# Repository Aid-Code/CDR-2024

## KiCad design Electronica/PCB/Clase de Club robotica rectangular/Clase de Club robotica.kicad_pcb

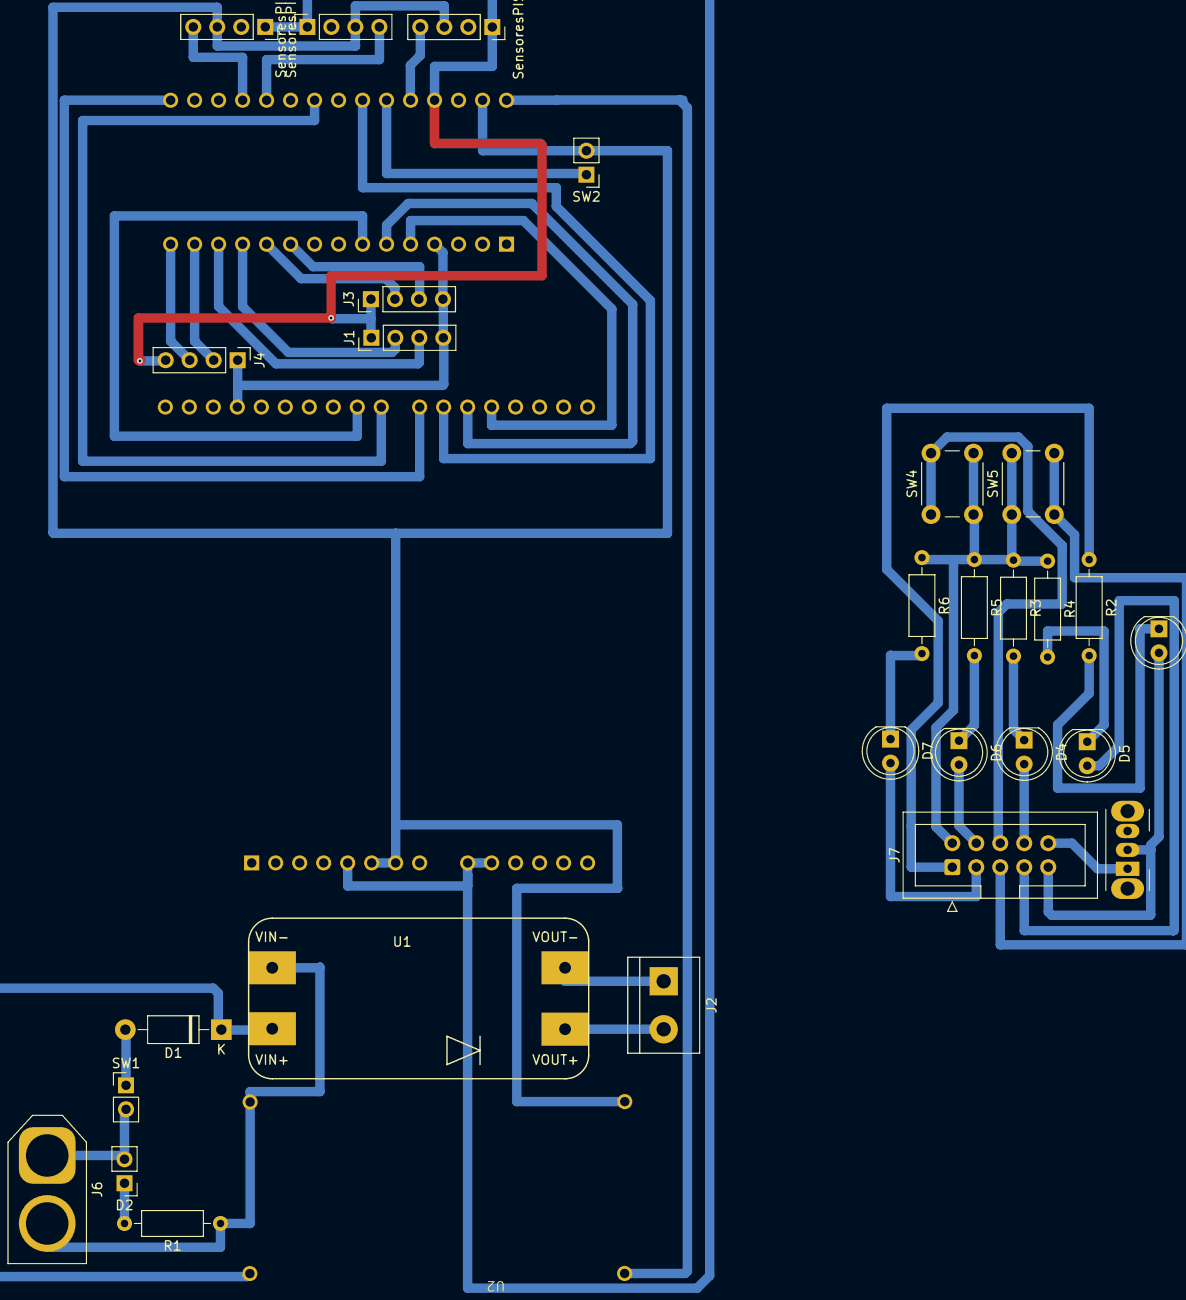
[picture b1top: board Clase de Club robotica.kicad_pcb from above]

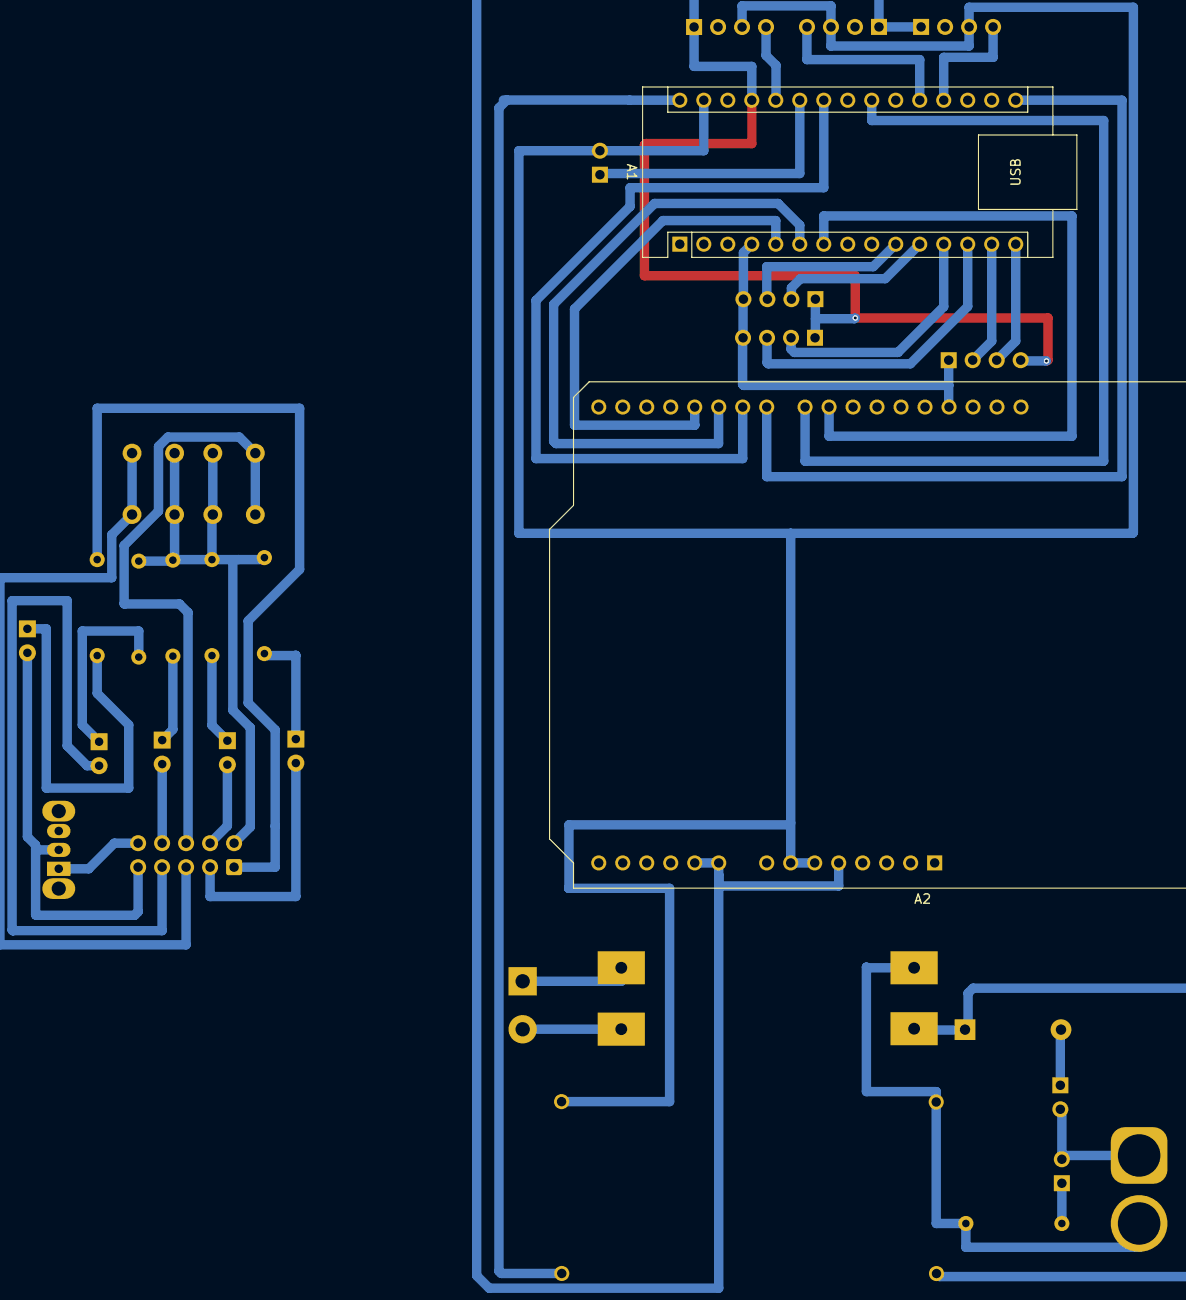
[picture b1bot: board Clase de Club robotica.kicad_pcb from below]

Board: 2 copper layers, 31 parts (2 on the bottom side), 39 nets.

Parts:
A1: Arduino_Nano_v3.x; Arduino_Nano
A2: MONSTER SHIELD; Arduino_UNO_R3
D1: 1N4007; D_DO-41_SOD81_P10.16mm_Horizontal
D2: LED; PinHeader_1x02_P2.54mm_Vertical
D3, D4, D5, D6, D7: LED; LED_D5.0mm
J1: Ultrasonico 1; PinHeader_1x04_P2.54mm_Vertical
J2: Screw_Terminal_01x02; TerminalBlock_bornier-2_P5.08mm
J3: Ultrasonico 2; PinHeader_1x04_P2.54mm_Vertical
J4: Ultrasonico 3; PinHeader_1x04_P2.54mm_Vertical
J6: Screw_Terminal_01x02; AMASS_XT60-M_1x02_P7.20mm_Vertical
J7: Conn_02x05_Counter_Clockwise; IDC-Header_2x05_P2.54mm_Vertical
R1: R_US; R_Axial_DIN0207_L6.3mm_D2.5mm_P10.16mm_Horizontal
R2: 660; R_Axial_DIN0207_L6.3mm_D2.5mm_P10.16mm_Horizontal
R3, R4, R5, R6: 220; R_Axial_DIN0207_L6.3mm_D2.5mm_P10.16mm_Horizontal
SW1: SW_SPST; PinHeader_1x02_P2.54mm_Vertical
SW2: SW_Push; PinHeader_1x02_P2.54mm_Vertical
SW3: SW_SPST; SW_Slide_SPDT_Angled_CK_OS102011MA1Q
SW4, SW5: SW_Push; SW_PUSH_6mm
SensoresPISO1, SensoresPISO2, SensoresPISO3: Conn_01x04; PinSocket_1x04_P2.54mm_Vertical
U1: MT3608_module
U2: Step Down

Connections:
+5V: A1.27 (+5V), A2.5 (+5V), A2.9 (A0), A2.10 (A1), J1.1, J3.1, J4.4, SensoresPISO1.1, SensoresPISO2.1, SensoresPISO3.1
AIN1 MONSTER SHIELD: A1.16 (D13), A2.22 (D7)
AIN2 MONSTER SHIELD: A1.22 (A3), A2.23 (D8)
BIN 1 MONSTER SHIELD: A1.5 (D2), A2.19 (D4)
BIN 2 MONSTER SHIELD: A1.7 (D4), A2.24 (D9)
BOTON: A1.25 (A6), SW2.1
ECHO 1: A1.13 (D10), J1.3
ECHO 2: A1.10 (D7), J3.3
ECHO 3: A1.14 (D11), J4.2
Earth: J6.2, J7.1, R1.1, R2.1, U1.VIN-, U2.VIN-
GND: A1.4 (GND), A1.29 (GND), A2.6 (GND), A2.7 (GND), A2.29 (GND), J1.4, J3.4, J4.1, J7.2, R3.1, R4.1, R5.1, R6.1, SW2.2, SW4.2, SW5.1, SensoresPISO1.3, SensoresPISO2.3, SensoresPISO3.3, U2.VOUT-
unnamed: D1.2 (A), SW1.1 (A)
unnamed: D2.2 (A), J6.1, SW1.2 (B)
unnamed: D2.1 (K), R1.2
unnamed: D3.2 (A), J7.9, SW3.2 (B)
unnamed: D3.1 (K), R2.2
unnamed: D4.2 (A), J7.8
unnamed: D4.1 (K), R3.2
unnamed: D5.2 (A), J7.7
unnamed: D5.1 (K), R4.2
unnamed: D6.2 (A), J7.4
unnamed: D6.1 (K), R5.2
unnamed: D7.2 (A), J7.3
unnamed: D7.1 (K), R6.2
unnamed: J2.1, U1.VOUT-
unnamed: J2.2, U1.VOUT+
unnamed: J7.5, SW5.2
unnamed: J7.6, SW4.1
unnamed: J7.10, SW3.1 (A)
PWM A MONSTER SHIELD: A1.6 (D3), A2.20 (D5)
PWM B MONSTER SHIELD: A1.24 (A5), A2.21 (D6)
SENSOR DE PISO 1: A1.26 (A7), SensoresPISO1.4
SENSOR DE PISO 2: A1.20 (A1), SensoresPISO2.4
SENSOR DE PISO 3: A1.19 (A0), SensoresPISO3.4
STEP DOWN: D1.1 (K), U1.VIN+, U2.VIN+
TRIG 1: A1.12 (D9), J1.2
TRIG 2: A1.11 (D8), J3.2
TRIG 3: A1.15 (D12), J4.3
VIN: A1.30 (VIN), U2.VOUT+

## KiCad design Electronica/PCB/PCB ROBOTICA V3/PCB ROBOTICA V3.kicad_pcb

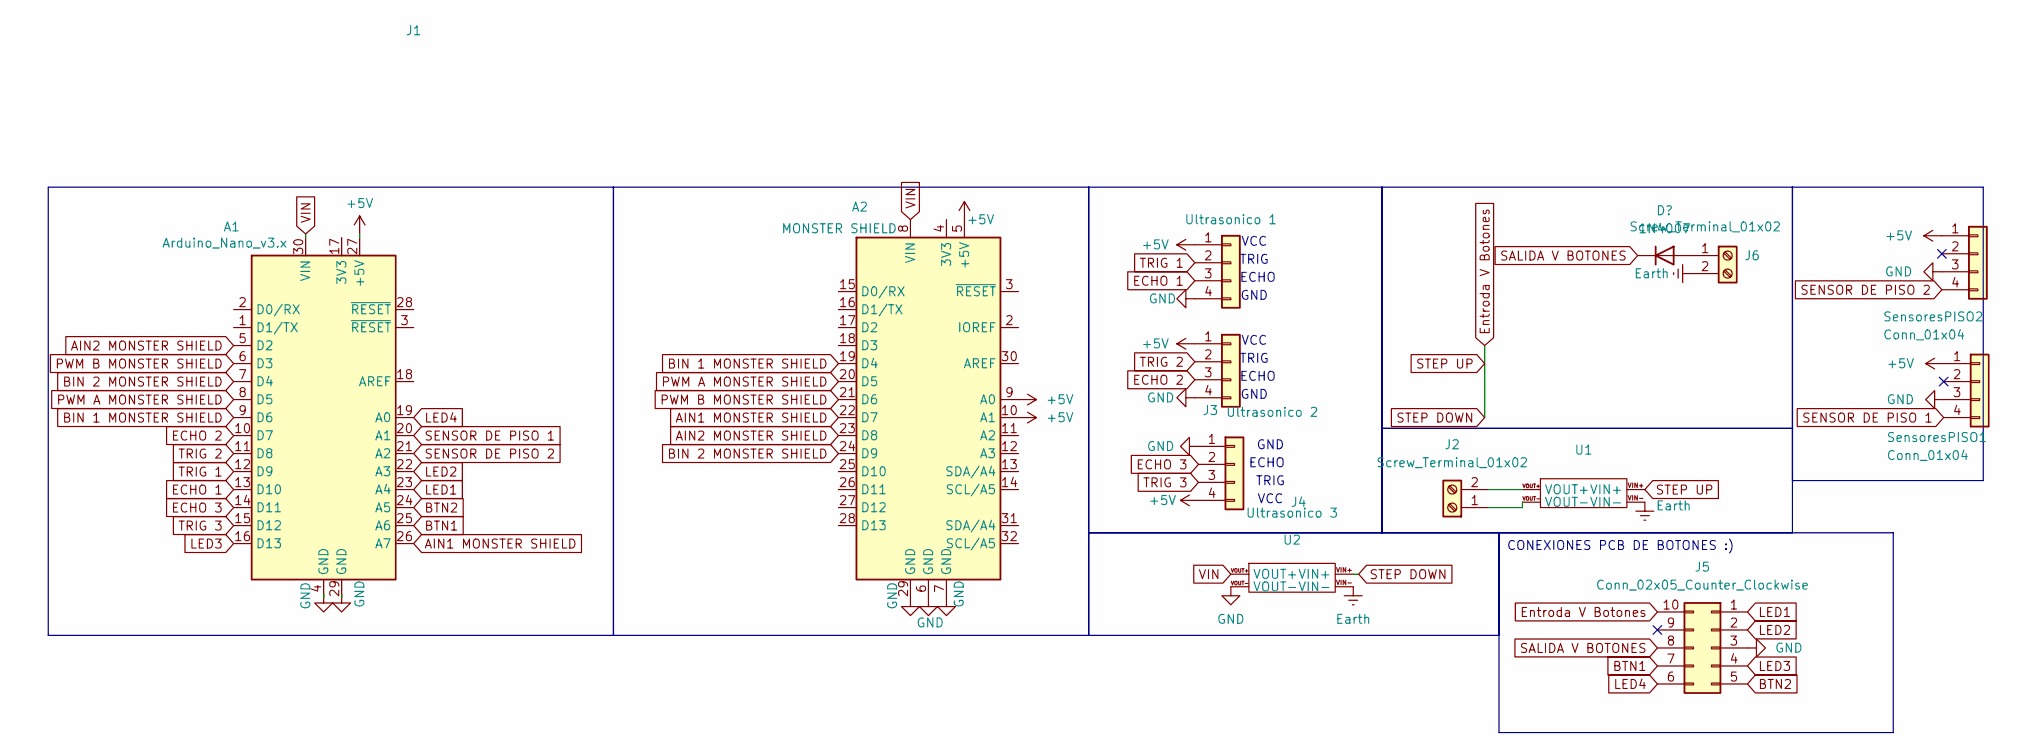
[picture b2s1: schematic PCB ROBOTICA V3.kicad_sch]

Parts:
A1: Arduino_Nano_v3.x; Arduino_Nano
A2: MONSTER SHIELD; Arduino_UNO_R3
J1: Ultrasonico 1; PinHeader_1x04_P2.54mm_Vertical
J2: Screw_Terminal_01x02; TerminalBlock_bornier-2_P5.08mm
J3: Ultrasonico 2; PinHeader_1x04_P2.54mm_Vertical
J4: Ultrasonico 3; PinHeader_1x04_P2.54mm_Vertical
J5: Conn_02x05_Counter_Clockwise; IDC-Header_2x05_P2.54mm_Vertical
J6: Screw_Terminal_01x02; AMASS_XT60-M_1x02_P7.20mm_Vertical
SensoresPISO1, SensoresPISO2: Conn_01x04; PinSocket_1x04_P2.54mm_Vertical
U1: MT3608_module
U2: Step Down

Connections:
+5V: A1.27 (+5V), A2.5 (+5V), A2.9 (A0), A2.10 (A1), J1.1, J3.1, J4.4, SensoresPISO1.1, SensoresPISO2.1
AIN1 MONSTER SHIELD: A1.26 (A7), A2.22 (D7)
AIN2 MONSTER SHIELD: A1.5 (D2), A2.23 (D8)
BIN 1 MONSTER SHIELD: A1.9 (D6), A2.19 (D4)
BIN 2 MONSTER SHIELD: A1.7 (D4), A2.24 (D9)
BTN1: A1.25 (A6), J5.7
BTN2: A1.24 (A5), J5.5
ECHO 1: A1.13 (D10), J1.3
ECHO 2: A1.10 (D7), J3.3
ECHO 3: A1.14 (D11), J4.2
Earth: J6.2, U1.VIN-, U2.VIN-
Entroda V Botones: J5.10, U1.VIN+, U2.VIN+
GND: A1.4 (GND), A1.29 (GND), A2.6 (GND), A2.7 (GND), A2.29 (GND), J1.4, J3.4, J4.1, J5.3, SensoresPISO1.3, SensoresPISO2.3, U2.VOUT-
LED1: A1.23 (A4), J5.1
LED2: A1.22 (A3), J5.2
LED3: A1.16 (D13), J5.4
LED4: A1.19 (A0), J5.6
unnamed 17: J6.1; also elsewhere on the board
unnamed: J2.1, U1.VOUT-
unnamed: J2.2, U1.VOUT+
PWM A MONSTER SHIELD: A1.8 (D5), A2.20 (D5)
PWM B MONSTER SHIELD: A1.6 (D3), A2.21 (D6)
SALIDA V BOTONES: J5.8; also elsewhere on the board
SENSOR DE PISO 1: A1.20 (A1), SensoresPISO1.4
SENSOR DE PISO 2: A1.21 (A2), SensoresPISO2.4
TRIG 1: A1.12 (D9), J1.2
TRIG 2: A1.11 (D8), J3.2
TRIG 3: A1.15 (D12), J4.3
VIN: A1.30 (VIN), A2.8 (VIN), U2.VOUT+

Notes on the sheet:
CONEXIONES PCB DE BOTONES :)
ECHO
TRIG
GND
VCC

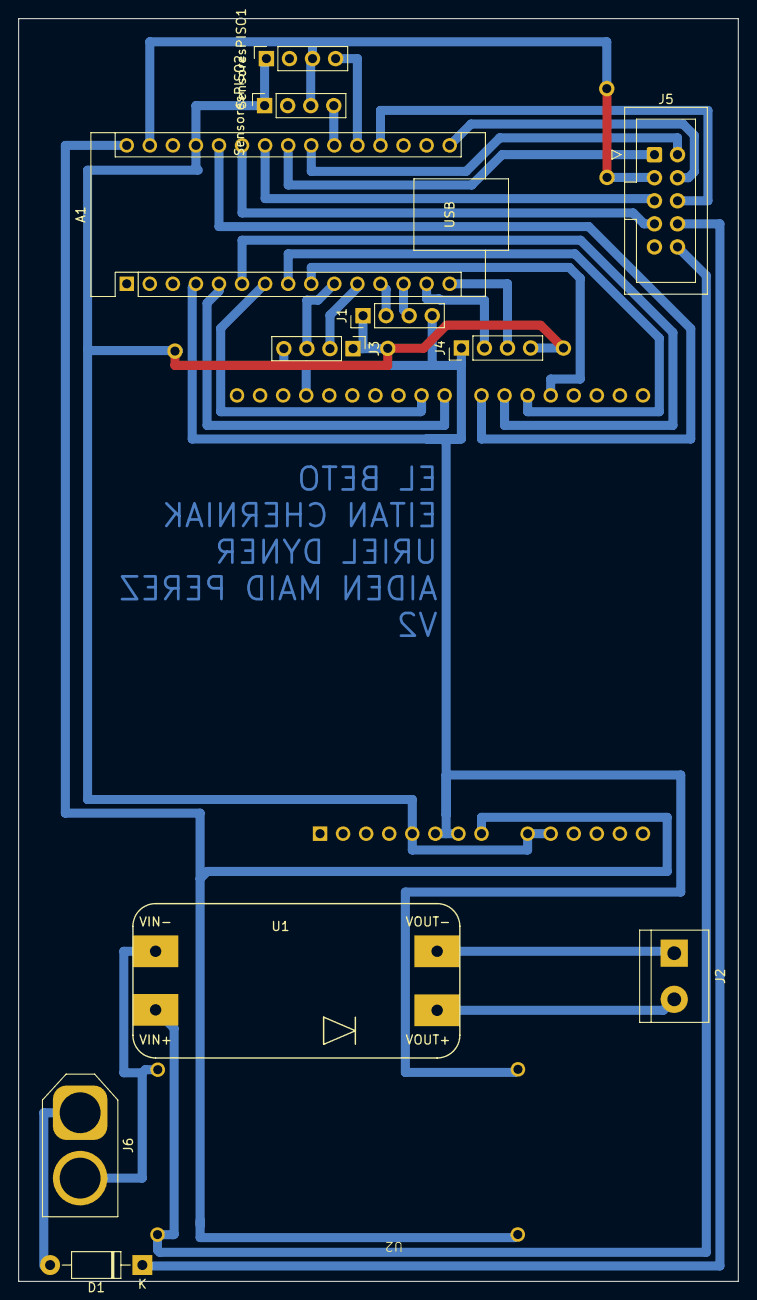
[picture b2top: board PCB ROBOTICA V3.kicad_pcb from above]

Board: 2 copper layers, 79.2 x 139.1 mm, 13 parts (1 on the bottom side), 29 nets.

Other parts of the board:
D1: 1N4007; D_DO-41_SOD81_P10.16mm_Horizontal

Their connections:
unnamed 17: D1.2 (A); also elsewhere on the board
SALIDA V BOTONES: D1.1 (K); also elsewhere on the board

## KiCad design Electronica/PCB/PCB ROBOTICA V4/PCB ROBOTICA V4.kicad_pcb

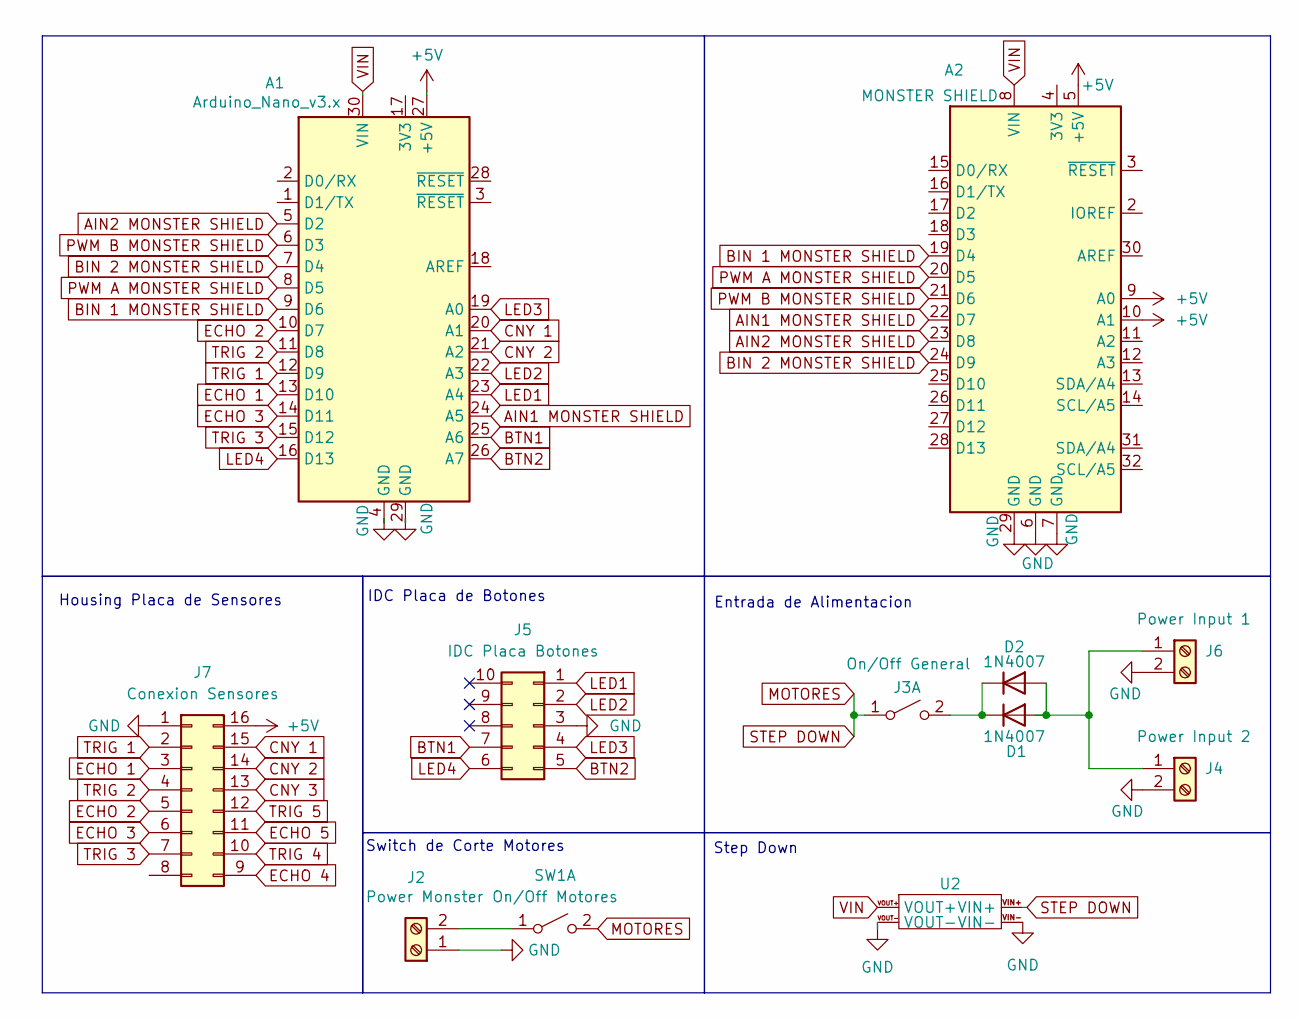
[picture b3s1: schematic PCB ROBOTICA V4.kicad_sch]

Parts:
A1: Arduino_Nano_v3.x; Arduino_Nano
A2: MONSTER SHIELD; Arduino_UNO_R3
D1, D2: 1N4007; D_DO-41_SOD81_P10.16mm_Horizontal
J2: Power Monster; TerminalBlock_bornier-2_P5.08mm
J3: On/Off General; TerminalBlock_bornier-2_P5.08mm
J4: Power Input 2; AMASS_XT60-M_1x02_P7.20mm_Vertical
J5: IDC Placa Botones; IDC-Header_2x05_P2.54mm_Vertical
J6: Power Input 1; AMASS_XT60-M_1x02_P7.20mm_Vertical
J7: Conexion Sensores; PinHeader_2x08_P2.54mm_Horizontal
SW1: On/Off Motores; SW_Slide_SPDT_Angled_CK_OS102011MA1Q
U2: Step Down

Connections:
+5V: A1.27 (+5V), A2.5 (+5V), A2.9 (A0), A2.10 (A1), J7.16
AIN1 MONSTER SHIELD: A1.24 (A5), A2.22 (D7)
AIN2 MONSTER SHIELD: A1.5 (D2), A2.23 (D8)
BIN 1 MONSTER SHIELD: A1.9 (D6), A2.19 (D4)
BIN 2 MONSTER SHIELD: A1.7 (D4), A2.24 (D9)
BTN1: A1.25 (A6), J5.7
BTN2: A1.26 (A7), J5.5
CNY 1: A1.20 (A1), J7.15
CNY 2: A1.21 (A2), J7.14
CNY 3: J7.13
ECHO 1: A1.13 (D10), J7.3
ECHO 2: A1.10 (D7), J7.5
ECHO 3: A1.14 (D11), J7.6
ECHO 4: J7.9
ECHO 5: J7.11
GND: A1.4 (GND), A1.29 (GND), A2.6 (GND), A2.7 (GND), A2.29 (GND), J2.1, J4.2, J5.3, J6.2, J7.1, U2.VIN-, U2.VOUT-
LED1: A1.23 (A4), J5.1
LED2: A1.22 (A3), J5.2
LED3: A1.19 (A0), J5.4
LED4: A1.16 (D13), J5.6
MOTORES: J3.1 (A), SW1.2 (B), U2.VIN+
unnamed: D1.2 (A), D2.2 (A), J4.1, J6.1
unnamed: D1.1 (K), D2.1 (K), J3.2 (B)
unnamed 26: J2.2, SW1.1 (A); also elsewhere on the board
PWM A MONSTER SHIELD: A1.8 (D5), A2.20 (D5)
PWM B MONSTER SHIELD: A1.6 (D3), A2.21 (D6)
TRIG 1: A1.12 (D9), J7.2
TRIG 2: A1.11 (D8), J7.4
TRIG 3: A1.15 (D12), J7.7
TRIG 4: J7.10
TRIG 5: J7.12
VIN: A1.30 (VIN), A2.8 (VIN), U2.VOUT+

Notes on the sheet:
Switch de Corte Motores
Entrada de Alimentacion
Step Down
Housing Placa de Sensores
IDC Placa de Botones

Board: 2 copper layers, 12 parts (1 on the bottom side), 27 nets, no tracks yet.

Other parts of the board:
U1: MT3608_module

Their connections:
unnamed 26: U1.VOUT+; also elsewhere on the board

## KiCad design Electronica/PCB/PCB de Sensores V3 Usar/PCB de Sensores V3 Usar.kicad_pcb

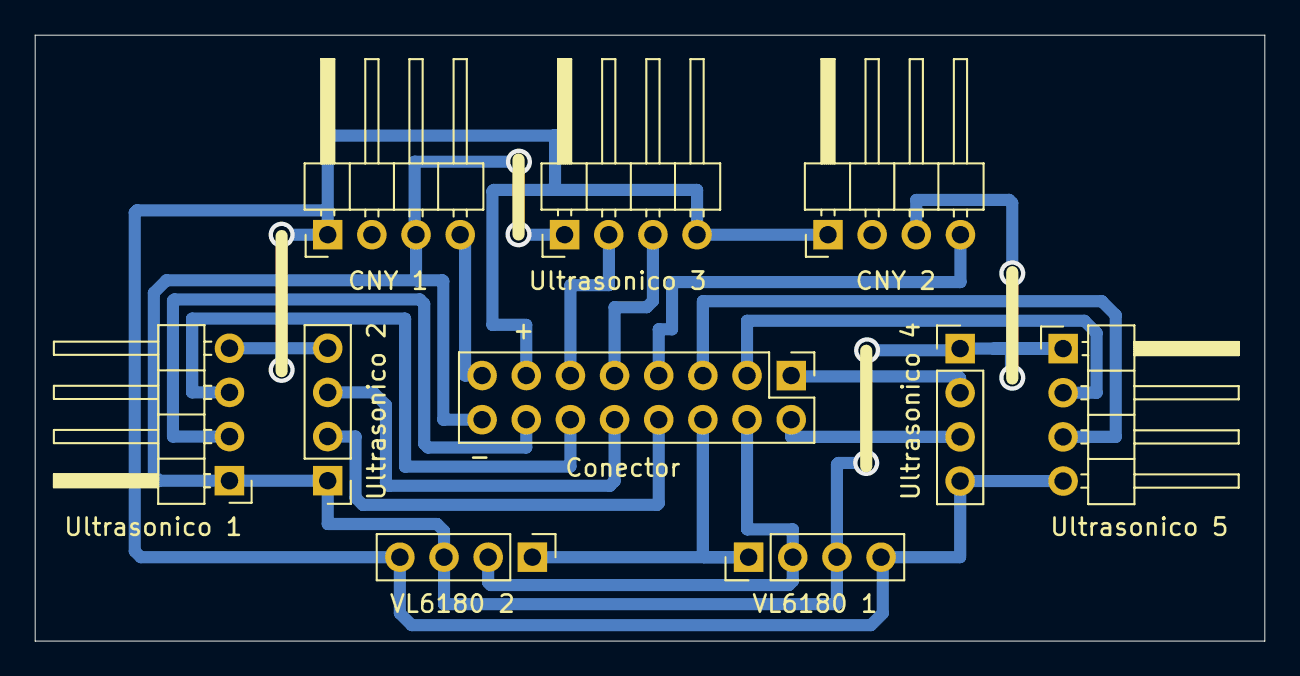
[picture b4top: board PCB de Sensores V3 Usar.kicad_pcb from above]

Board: 2 copper layers, 70.7 x 34.9 mm, 10 parts (0 on the bottom side), 16 nets.

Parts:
CNY 1: CNY1; PinHeader_1x04_P2.54mm_Horizontal
CNY 2: CNY2; PinHeader_1x04_P2.54mm_Horizontal
Conector: Conexion Sensores; PinHeader_2x08_P2.54mm_Vertical
Ultrasonico 1: ULTRASONICO1; PinHeader_1x04_P2.54mm_Horizontal
Ultrasonico 2: ULTRASONICO2; PinHeader_1x04_P2.54mm_Vertical
Ultrasonico 3: ULTRASONICO3; PinHeader_1x04_P2.54mm_Horizontal
Ultrasonico 4: ULTRASONICO4; PinHeader_1x04_P2.54mm_Vertical
Ultrasonico 5: ULTRASONICO5; PinHeader_1x04_P2.54mm_Horizontal
VL6180 1: VL6180 1; PinHeader_1x04_P2.54mm_Vertical
VL6180 2: VL6180 2; PinHeader_1x04_P2.54mm_Vertical

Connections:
+5V: CNY 1.1, CNY 2.1, Conector.13, Ultrasonico 1.4, Ultrasonico 2.4, Ultrasonico 3.4, Ultrasonico 4.4, Ultrasonico 5.4, VL6180 1.4, VL6180 2.4
CNY 1: CNY 1.4, Conector.15
CNY 2: CNY 2.4, Conector.7
ECHO 1: Conector.14, Ultrasonico 1.2
ECHO 2: Conector.8, Ultrasonico 2.2
ECHO 3: Conector.11, Ultrasonico 3.2
ECHO 4: Conector.1, Ultrasonico 4.2
ECHO 5: Conector.3, Ultrasonico 5.2
GND: CNY 1.3, CNY 2.3, Conector.16, Ultrasonico 1.1, Ultrasonico 2.1, Ultrasonico 3.1, Ultrasonico 4.1, Ultrasonico 5.1, VL6180 1.3, VL6180 2.3
SCL: Conector.4, VL6180 1.2, VL6180 2.2
SDA: Conector.6, VL6180 1.1, VL6180 2.1
TRIG 1: Conector.12, Ultrasonico 1.3
TRIG 2: Conector.10, Ultrasonico 2.3
TRIG 3: Conector.9, Ultrasonico 3.3
TRIG 4: Conector.2, Ultrasonico 4.3
TRIG 5: Conector.5, Ultrasonico 5.3

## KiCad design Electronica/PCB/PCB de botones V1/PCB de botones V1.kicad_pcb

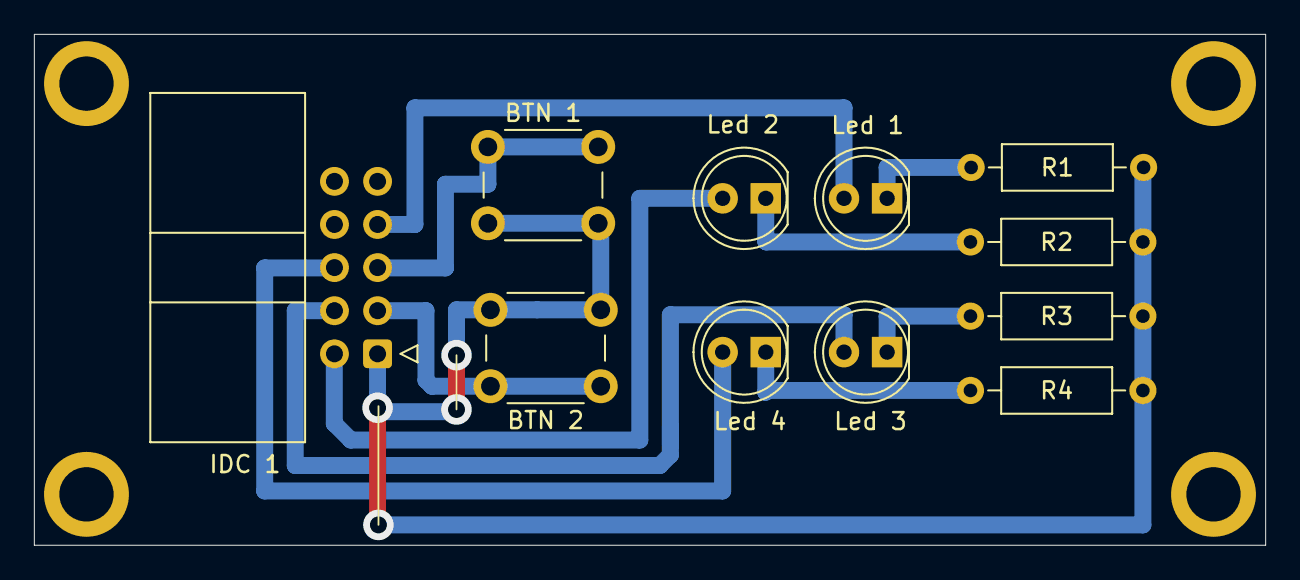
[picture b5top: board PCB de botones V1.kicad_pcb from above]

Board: 2 copper layers, 72.5 x 30.1 mm, 11 parts (0 on the bottom side), 11 nets.

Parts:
BTN 1, BTN 2: SW_Push; SW_PUSH_6mm
IDC 1: IDC Placa Botones; IDC-Header_2x05_P2.54mm_Horizontal
Led 1, Led 2, Led 3, Led 4: LED; LED_D5.0mm
R1, R2, R3, R4: R_US; R_Axial_DIN0207_L6.3mm_D2.5mm_P10.16mm_Horizontal

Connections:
BTN1: BTN 1.1, IDC 1.5
BTN2: BTN 2.1, IDC 1.3
GND: BTN 1.2, BTN 2.2, IDC 1.1, R1.1, R2.1, R3.1, R4.1
LED1: IDC 1.7, Led 1.2 (A)
LED2: IDC 1.2, Led 2.2 (A)
LED3: IDC 1.4, Led 3.2 (A)
LED4: IDC 1.6, Led 4.2 (A)
unnamed: Led 1.1 (K), R1.2
unnamed: Led 2.1 (K), R2.2
unnamed: Led 3.1 (K), R3.2
unnamed: Led 4.1 (K), R4.2

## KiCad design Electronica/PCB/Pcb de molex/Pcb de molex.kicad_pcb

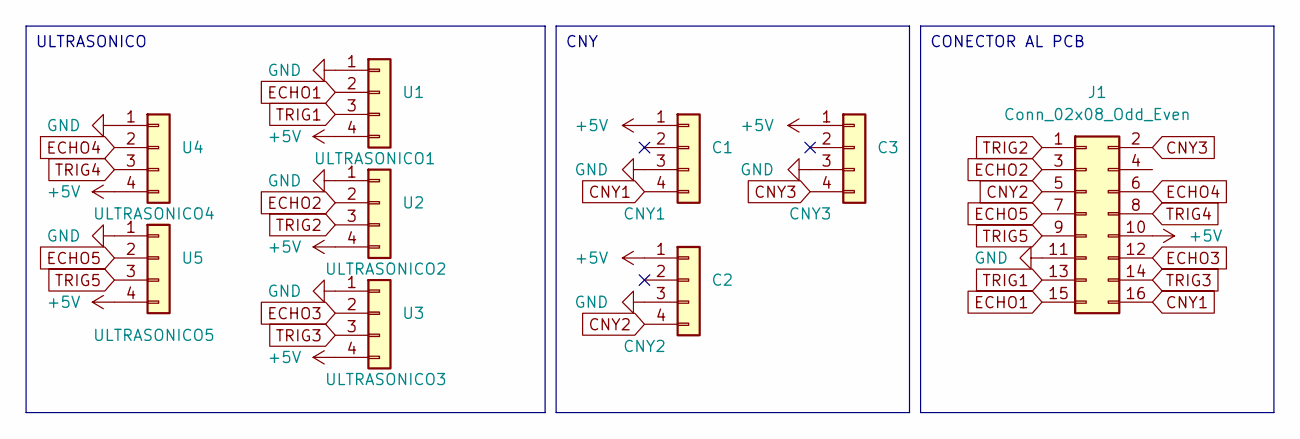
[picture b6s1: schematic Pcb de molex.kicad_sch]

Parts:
C1: CNY1; PinHeader_1x04_P2.54mm_Horizontal
C2: CNY2; PinHeader_1x04_P2.54mm_Horizontal
C3: CNY3; PinHeader_1x04_P2.54mm_Horizontal
J1: Conn_02x08_Odd_Even; PinHeader_2x08_P2.54mm_Horizontal
U1: ULTRASONICO1; PinHeader_1x04_P2.54mm_Horizontal
U2: ULTRASONICO2; PinHeader_1x04_P2.54mm_Horizontal
U3: ULTRASONICO3; PinHeader_1x04_P2.54mm_Horizontal
U4: ULTRASONICO4; PinHeader_1x04_P2.54mm_Horizontal
U5: ULTRASONICO5; PinHeader_1x04_P2.54mm_Vertical

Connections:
+5V: C1.1, C2.1, C3.1, J1.10, U1.4, U2.4, U3.4, U4.4, U5.4
CNY1: C1.4, J1.16
CNY2: C2.4, J1.5
CNY3: C3.4, J1.2
ECHO1: J1.15, U1.2
ECHO2: J1.3, U2.2
ECHO3: J1.12, U3.2
ECHO4: J1.6, U4.2
ECHO5: J1.7, U5.2
GND: C1.3, C2.3, C3.3, J1.11, U1.1, U2.1, U3.1, U4.1, U5.1
TRIG1: J1.13, U1.3
TRIG2: J1.1, U2.3
TRIG3: J1.14, U3.3
TRIG4: J1.8, U4.3
TRIG5: J1.9, U5.3

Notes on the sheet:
CONECTOR AL PCB
ULTRASONICO
CNY

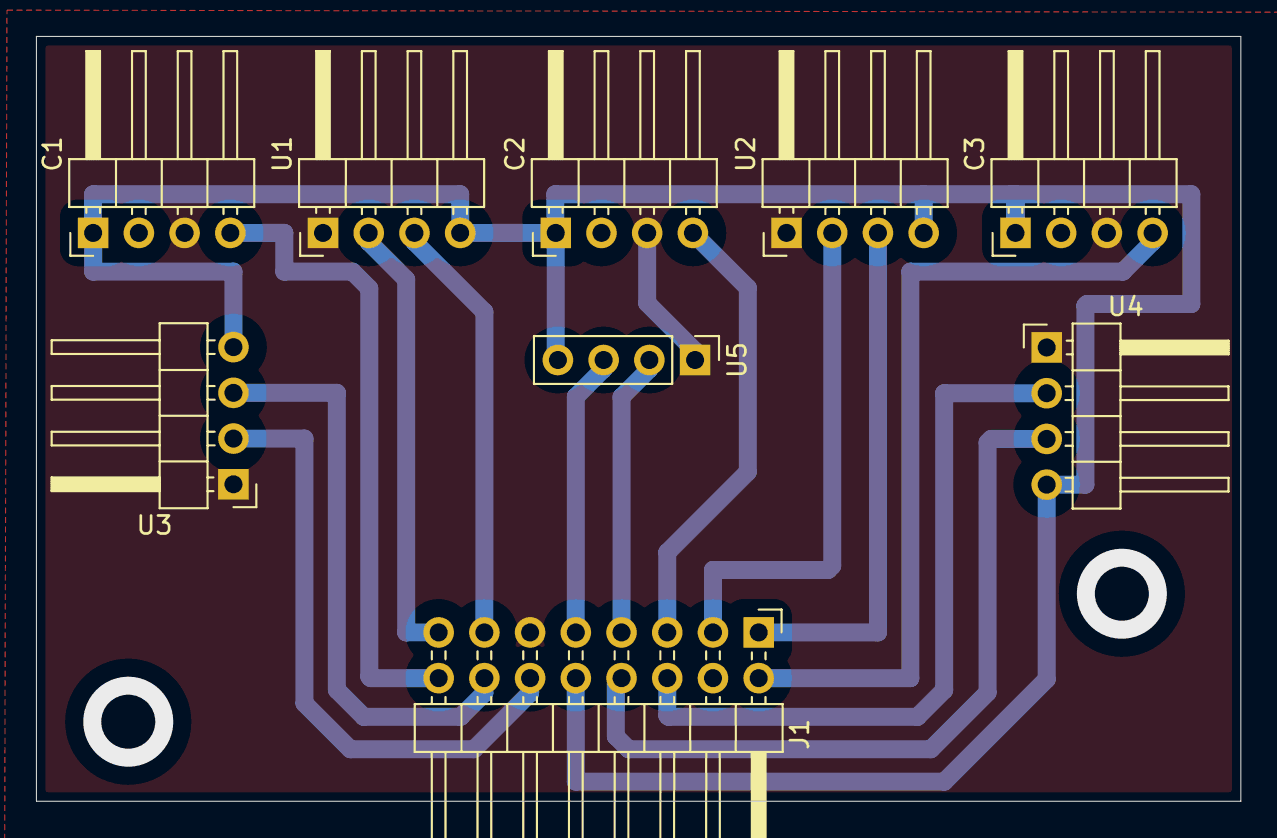
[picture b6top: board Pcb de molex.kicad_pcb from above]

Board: 2 copper layers, 66.9 x 42.5 mm, 9 parts (0 on the bottom side), 15 nets.
